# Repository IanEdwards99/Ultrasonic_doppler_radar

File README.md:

Ultrasonic CW Doppler RADAR for sports object velocity estimation and research purposes. A low-budget well-packaged portable RADAR is detailed in this repository from hardware to signal processing. This is a final year project contributing towards my degree in Electrical and Computer Engineering at the University of Cape Town, supervised by Dr Yunus Abdul Gaffar.

The application can load existing recorded RADAR data - this data can be found at the following Google Drive link:
https://drive.google.com/drive/folders/16D7cyREpJ_ywHIkBDAXUJWHujvHpHnOc?usp=sharing

For details on what experiments were carried out and thus what data was collected, read the final report in the repository.

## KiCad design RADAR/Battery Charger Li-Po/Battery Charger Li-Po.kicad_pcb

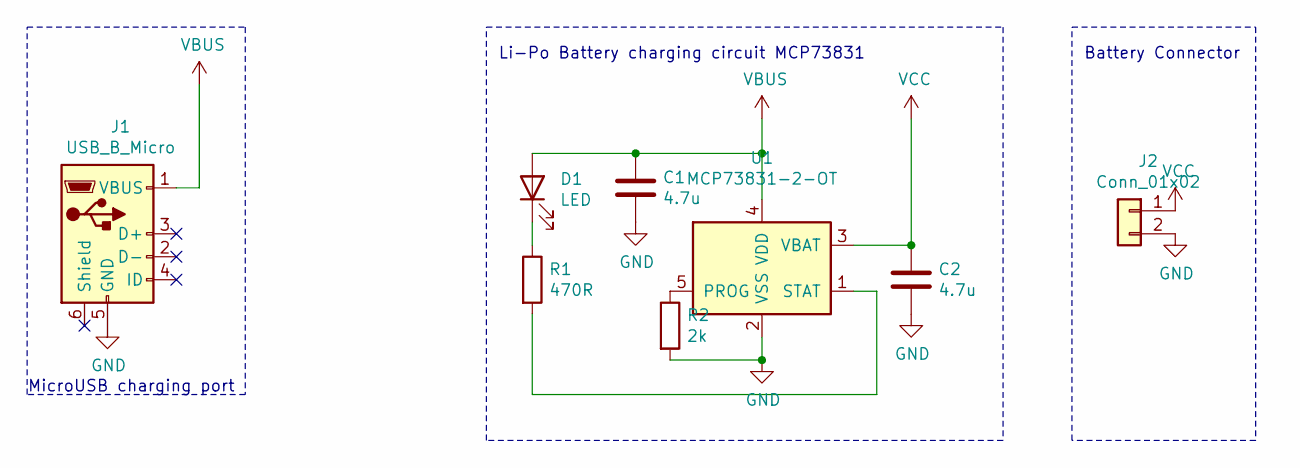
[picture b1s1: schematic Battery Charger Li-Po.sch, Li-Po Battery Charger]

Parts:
C1, C2: 4.7u; C_0805_2012Metric
D1: LED; LED_0805_2012Metric
J1: USB_B_Micro; USB_Micro-B_Molex-105017-0001
J2: Conn_01x02; JST_XH_B2B-XH-A_1x02_P2.50mm_Vertical
R1: 470R; R_0805_2012Metric
R2: 2k; R_0805_2012Metric
U1: MCP73831-2-OT; SOT-23-5

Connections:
GND: C1.1, C2.2, J1.5 (GND), J2.2, R2.2, U1.2 (VSS)
unnamed: D1.1 (K), R1.1
unnamed: R1.2, U1.1 (STAT)
unnamed: R2.1, U1.5 (PROG)
VBUS: C1.2, D1.2 (A), J1.1 (VBUS), U1.4 (VDD)
VCC: C2.1, J2.1, U1.3 (VBAT)

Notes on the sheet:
MicroUSB charging port
Li-Po Battery charging circuit MCP73831
Battery Connector

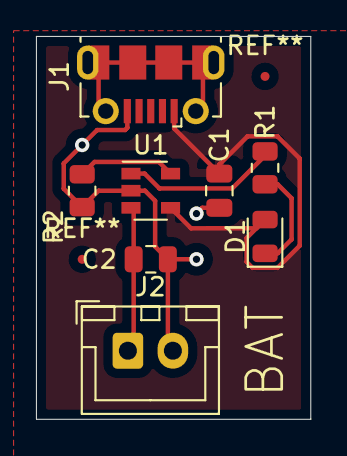
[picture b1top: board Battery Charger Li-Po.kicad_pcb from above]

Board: 2 copper layers, 15.2 x 21.3 mm, 8 parts (0 on the bottom side), 6 nets.

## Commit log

2021-10-22 Files added via upload - first commit
    Added code, hardware development and enclosure files.
2021-10-22 Add files via upload
    Added example data files to use.
2021-11-06 Add files via upload
    Uploaded test result data and PCB schematic
2021-11-06 Add files via upload
    Updated Demonstrator and made CWApp to operate continuously
